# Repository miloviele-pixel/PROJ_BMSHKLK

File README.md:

# PROJ_BMSHKLK

# Idea
I felt that my desk needed something to make it more productive, something like a macropad!

# Backgroud
I've never used Fusion 360 before, only TinkerCAD for some other projects that I tackled, and definitely never KiCAD or any sort of firmware app. I've always been super into engineering, but normally the mechanical part of it, never really the electronics side even though I've always wanted to try it. Turns out, this was the perfect oppurtunity!

# Specifications
BOM:
|             Item             | Quantity | Price (USD) | Link                                                                                                                                                                                                                                                                                                                                                                                                                                                                                                                                                                                                                             |
|:----------------------------:|:--------:|:-----------:|----------------------------------------------------------------------------------------------------------------------------------------------------------------------------------------------------------------------------------------------------------------------------------------------------------------------------------------------------------------------------------------------------------------------------------------------------------------------------------------------------------------------------------------------------------------------------------------------------------------------------------|
| Cherry MX style switch       | 8        | $4.99       | https://www.amazon.com/ZhouWang-Pre-Lubricated-Dustproof-Prints%E3%80%81MX-Mechanical/dp/B0FKB8ZVDF/ref=sr_1_6?crid=34AHI6JZVDYEM&dib=eyJ2IjoiMSJ9.c8DTc97-6-PQOYAIpY9ECzdGVGBmrR162vOvPsduZQ6Kfv8bj65KlQBjobA0NiFRgz90U7L__uRRKcNqaFUzVvYse4xGd_E68M_AzqJ_YvvhBnNQWna9LlaFXelYaaYP68RVAedvtUl9Zqgs5QZPzM61E3a2_MHsGy1vy674mwKQPQAXsRDN43bGJArX2HmJKflYX3h7l3hQS7c_lRrPdGWIR3PRuKRg7WLnHLde_G0.TFR-KDXvW53qOFqJGQtZaeXA92qfXh5zhibhBj81B8o&dib_tag=se&keywords=cherry%2BMX%2Bstyle%2Bswitches&qid=1770934331&sprefix=cherry%2Bmx%2Bstyle%2Bswitche%2Caps%2C148&sr=8-6&th=1                                                       |
| XIAO RP2040 micro controller | 1        | $9.99       | https://www.amazon.com/Microcontroller-Dual-Core-MicroPython-CircuitPython-Interfaces/dp/B09NNVNW7M/ref=sr_1_1_sspa?crid=2UH6QV95XZK6O&dib=eyJ2IjoiMSJ9.Hxs3jCHqokIXwzSfDn6Q00dVyEjPI8sSxCsrRDHxt6fyUCh67Fyrso_Ld2njShICikc0vjU1Eyrmfq8Ausz-JT-fY__Fqe0SQG-WvIPsXDBRHcBPSZevAhj9B3ztyLQtognSba8h48KMA6PuQnmTH4mlnkvYnUmFOVM3KRjwBMiIaQnNQP1IawroZJsMJRqeQ5FRJl9v7-K_cuS7FLeaI24hcXERm3jc0Obs2xmgPHA.dEO_Nosis4HtQ10Piu0fFdP19K7dik7NbQtHdFw-Pf4&dib_tag=se&keywords=XIAO%2BRP2040%2Bmicro%2Bcontroller&qid=1770934417&sprefix=xiao%2Brp2040%2Bmicro%2Bcontroll%2Caps%2C148&sr=8-1-spons&sp_csd=d2lkZ2V0TmFtZT1zcF9hdGY&th=1      |
| Blank DSA Keycaps            | 8        | $8.99       | https://www.amazon.com/Mechkeeb-Profile-Switches-Keyboard-Replacement/dp/B0BWDR7LQQ/ref=sr_1_1?crid=2GJOW524G4VSD&dib=eyJ2IjoiMSJ9.tT5boyBrpc59ULFeef9XlbsF_5rYQYF0D-7r6c3amwhcyqHmDPaiRDfgSQQuVXjKGYmc04ubLkz7OLDxpG5yfyWiWx25RYhgWyGzNnEDYyNnIYNAhYoYO8MPs84zx_zhtKhfRFmRk3OhnDyAuzj6nlh_HvKfQpxtyQLLJbKL7eESuLOS9dGkSeF6papSHPvfv133hpj5CzhFFQ_nmsmqtZhihvubTmIc1gUsLuASrCk.eRYoRv85Jr4JwbT6JHuQXAxNYGIWBIoxoq5RvbjFWJw&dib_tag=se&keywords=Blank%2BDSA%2BKeycaps&qid=1770934505&sprefix=blank%2Bdsa%2Bkeycaps%2Caps%2C196&sr=8-1&th=1                                                                                        |
| M3x16 Bolt                   | 4        | $7.56       | https://www.amazon.com/Socket-Screws-Bolts-Thread-100pcs/dp/B07CMP5398/ref=sr_1_4?crid=20TC5VB2EEHAZ&dib=eyJ2IjoiMSJ9.uBGfQtBZ3h_jJZDPvZGj1GjvxYb4GZ2psA9xbA07FVJDkzUxby-t8Z4cUq1H4L3rRUToWFhyYL6DW_gGg6T2J2zgXSHsnjNNY4CzMD_F1uUBnXG5tg15JOpvQ34H_SWc9lGGSBzC51ocR8K5FTDxeiFoIiv0xe_V0g6hj60MY5zEyGJWZrrOhLXflIsifY-lSYxF17gXWf6bWkEFp0BJ_FTH-JyejfCIqU5-DmHcGls.gmOGTmWmZhPCHoOQE_Z5prtBFfS_07x1UF7IaiGwPsU&dib_tag=se&keywords=M3x16%2BBolt&qid=1770934584&sprefix=m3x16%2Bbolt%2Caps%2C192&sr=8-4&th=1                                                                                                                       |
| M3 Heatsets                  | 4        | $9.99       | https://www.amazon.com/HANGLIFE-Heat-Set-Threaded-Printing-Components/dp/B0CS6VZYL8/ref=sr_1_2_sspa?crid=Q8PWVLZZRWU9&dib=eyJ2IjoiMSJ9.x2ixhjBhT2UdNb3dlqncQkM4xXsHcgpwC6-IvO5RkCGVgV7Tp4sLoix1uILlBkftyVCoITR3m_lRwadzVp8wU-r6xdccohIAAKx-lgdvmqnMBS2bzQVE-rg2weWgLXT6N_4vSo-ieGqe-IMbdc-byti8wJh0uliyO27fmPl69fOh1SqXy4-2QC9SymUG2uIbl0S2CUvfpNltm9QLls9TS-G7JgvSfv5toCL2t19oVfTgdRyMANC7H7KfTSSs_OezzXmBPQKoTVMiDt1H419epkJgI2Yp3TvFr-BiNSHpMFQ.bGEEziBNFNwp5V4tAo_fFCoVR2Ku7mlV106-DAGbP7c&dib_tag=se&keywords=m3%2Bheadset&qid=1770934680&sprefix=m3%2Bheatset%2Caps%2C184&sr=8-2-spons&sp_csd=d2lkZ2V0TmFtZT1zcF9hdGY&th=1 |
| Through-hole 1N4148 Diodes   | 8        | $6.99       | https://www.amazon.com/100-Pieces-1N4148-Switching-High-Speed/dp/B079KJ91JZ/ref=sr_1_5_sspa?crid=22YV2PKNJZ275&dib=eyJ2IjoiMSJ9.1iwfzdTrjzmUwCxXq0RULhdrP7hNDsCQjJbwpiZk8cuexRKQh1vGKX7I0UMxgY06RcYnR9FHSaW2IYnp0K8pmNiAocjHWSSzqWvCNUTbLvjRHSprAkc6R_enLasQRwl7Vu52nOtjzCUZak8InU_ZTCYkBxPm9DKi_AA6exCA7rnS0tXEu7h5fjh5scbLVmLQkNWLjwygH9PJIakeBQG9gHf-suc550v2lppZA9_QTIc.vZBm9lfiBz-8DfmRkILmj8Ng8UTCQsqYfevL72mNDPc&dib_tag=se&keywords=Through-hole%2B1N4148%2BDiodes&qid=1770934741&sprefix=through-hole%2B1n4148%2Bdiodes%2Caps%2C174&sr=8-5-spons&sp_csd=d2lkZ2V0TmFtZT1zcF9tdGY&th=1                                    |

# Images

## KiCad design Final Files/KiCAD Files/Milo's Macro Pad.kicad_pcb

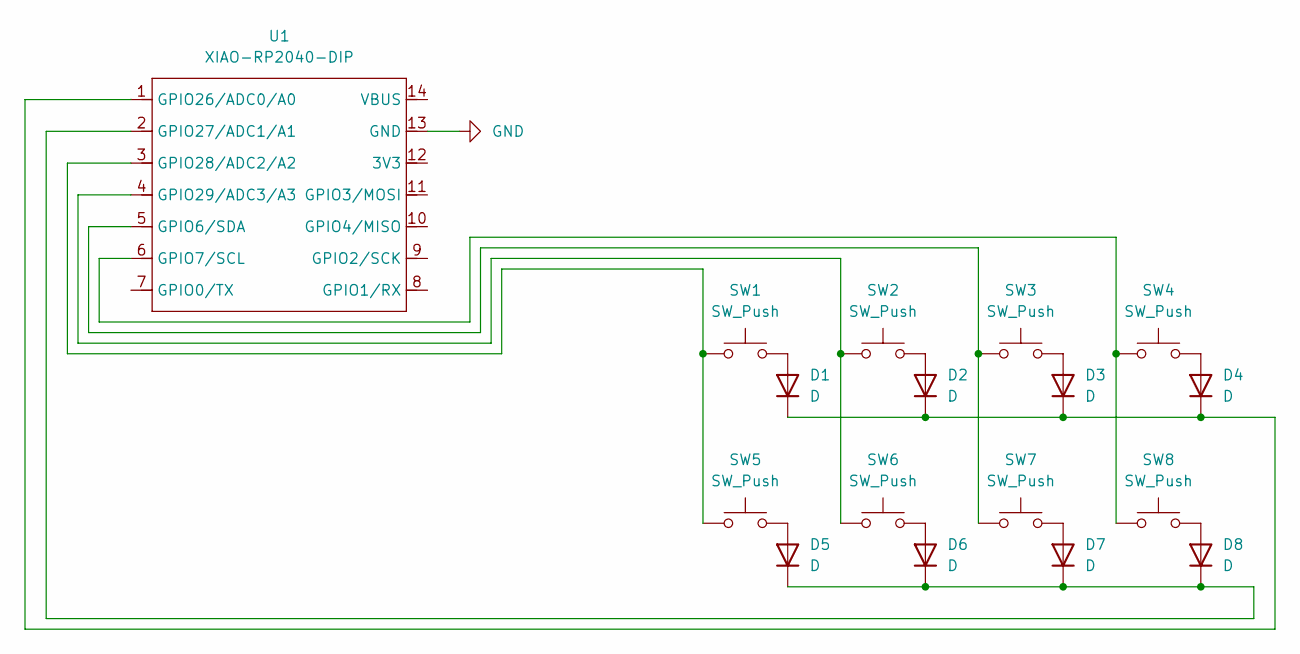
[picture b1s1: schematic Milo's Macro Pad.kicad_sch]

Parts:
D1, D2, D3, D4, D5, D6, D7, D8: D; D_T-1_P5.08mm_Horizontal
SW1, SW2, SW3, SW4, SW5, SW6, SW7, SW8: SW_Push; SW_Cherry_MX_1.00u_PCB
U1: XIAO-RP2040-DIP

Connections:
GND: U1.13 (GND)
unnamed: D1.2 (A), SW1.2
unnamed: D1.1 (K), D2.1 (K), D3.1 (K), D4.1 (K), U1.1 (GPIO26/ADC0/A0)
unnamed: D2.2 (A), SW2.2
unnamed: D3.2 (A), SW3.2
unnamed: D4.2 (A), SW4.2
unnamed: D5.2 (A), SW5.2
unnamed: D5.1 (K), D6.1 (K), D7.1 (K), D8.1 (K), U1.2 (GPIO27/ADC1/A1)
unnamed: D6.2 (A), SW6.2
unnamed: D7.2 (A), SW7.2
unnamed: D8.2 (A), SW8.2
unnamed: SW3.1, SW7.1, U1.5 (GPIO6/SDA)
unnamed: SW4.1, SW8.1, U1.6 (GPIO7/SCL)
unnamed: SW1.1, SW5.1, U1.3 (GPIO28/ADC2/A2)
unnamed: SW2.1, SW6.1, U1.4 (GPIO29/ADC3/A3)

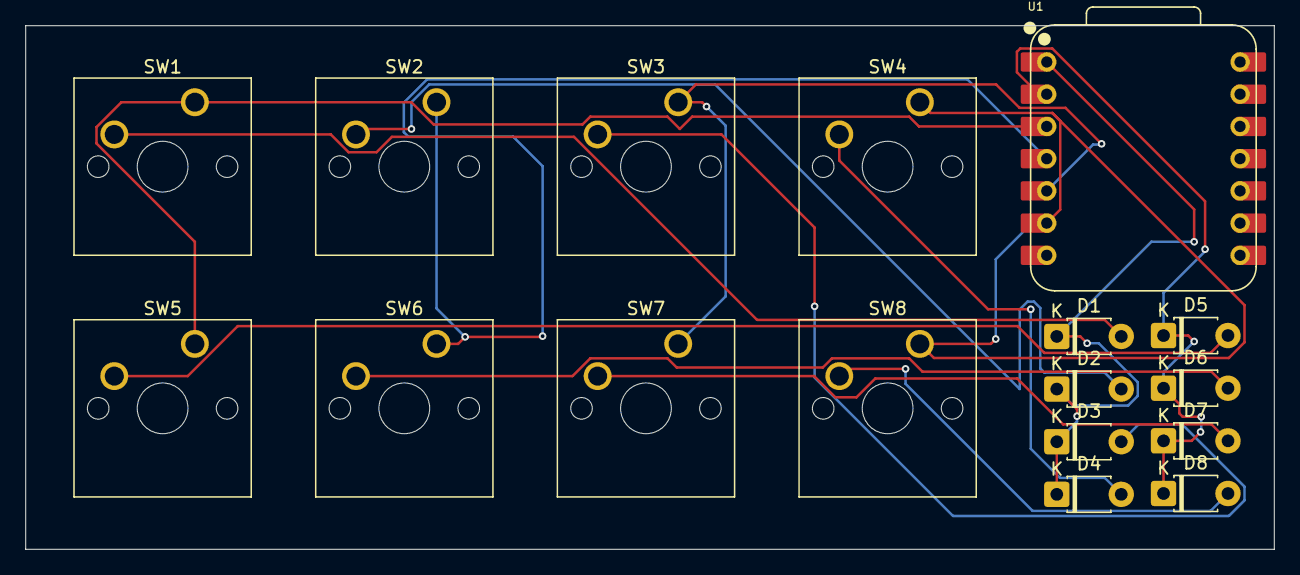
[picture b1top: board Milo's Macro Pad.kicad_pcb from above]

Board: 2 copper layers, 98.4 x 41.3 mm, 17 parts (0 on the bottom side), 14 nets.
